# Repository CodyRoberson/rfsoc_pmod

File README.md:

## ZCU111 RFSOC PMOD BREAKOUT BOARD
KiCad 6 design.

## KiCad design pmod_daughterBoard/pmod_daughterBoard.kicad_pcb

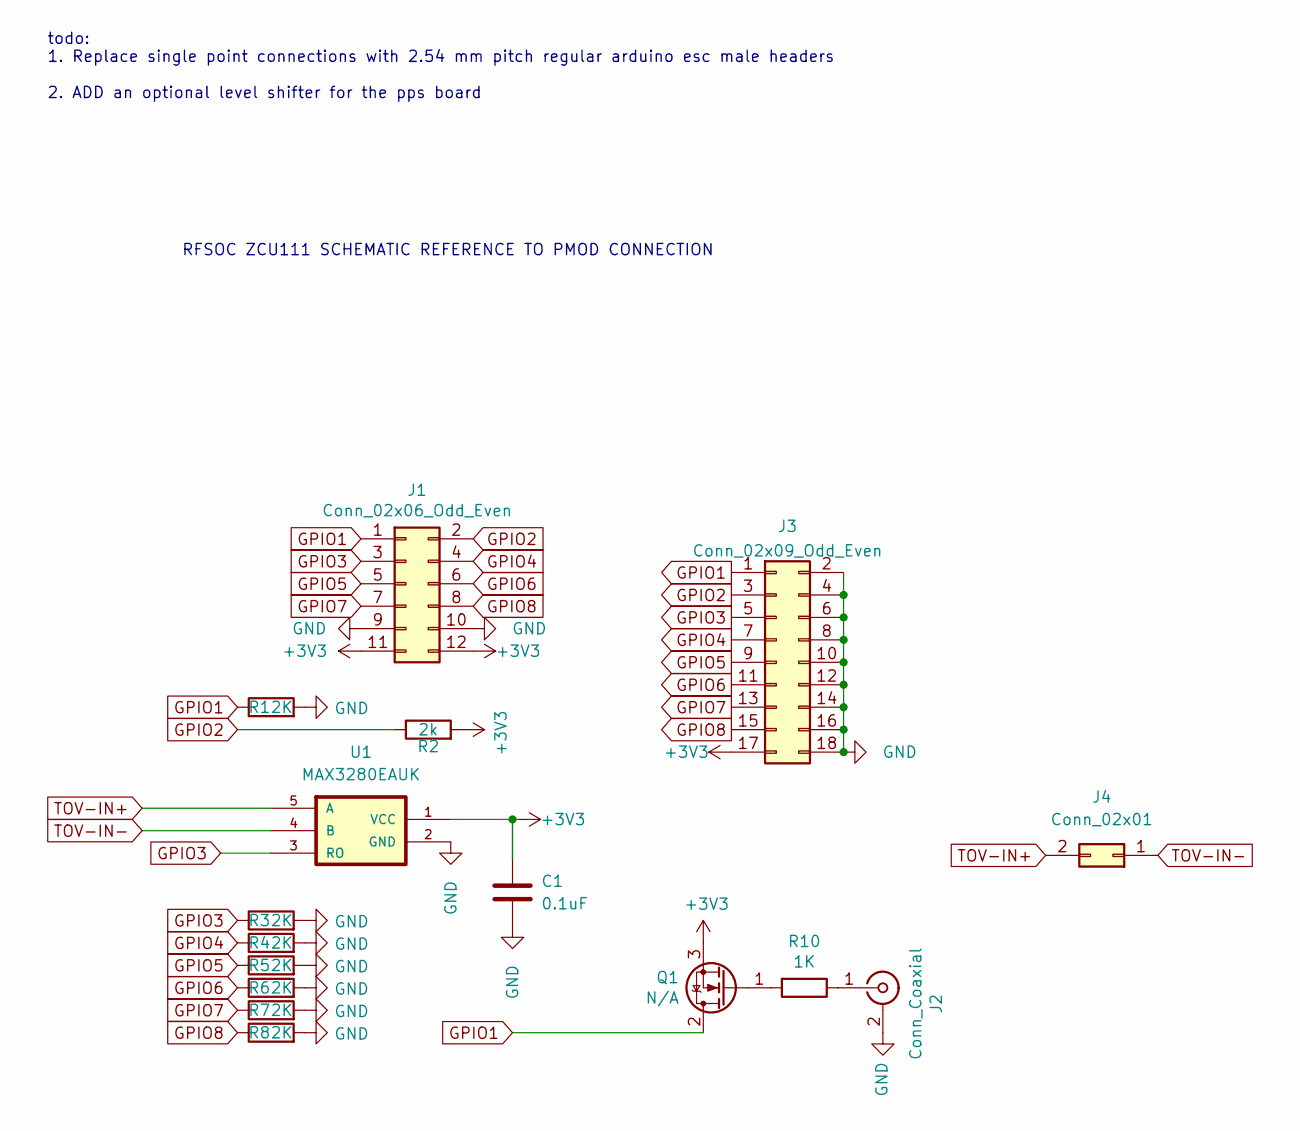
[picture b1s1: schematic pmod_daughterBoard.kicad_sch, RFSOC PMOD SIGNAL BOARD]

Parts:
C1: 0.1uF; C_0402_1005Metric
J1: Conn_02x06_Odd_Even; PinHeader_2x06_P2.54mm_Horizontal
J2: Conn_Coaxial; LINX_CONSMA001-SMD-G-T
J3: Conn_02x09_Odd_Even; PinHeader_2x09_P2.54mm_Vertical
J4: Conn_02x01; PinHeader_2x01_P2.54mm_Vertical
Q1: N/A; SOT-23; Part Number 78-SI2318DS-T1-BE3
R1, R3, R4, R5, R6, R7, R8: 2K; R_0402_1005Metric; Part Number 603-AC0402JR-072KL
R2: 2k; R_0402_1005Metric
R10: 1K; R_0402_1005Metric
U1: MAX3280EAUK; SOT95P280X145-5N; Part Number MAX3280EAUK+T

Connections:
+3V3: C1.2, J1.11, J1.12, J3.17, Q1.3 (S), R2.2, U1.1 (VCC)
GND: C1.1, J1.9, J1.10, J2.2 (Ext), J3.2, J3.4, J3.6, J3.8, J3.10, J3.12, J3.14, J3.16, J3.18, R1.2, R3.2, R4.2, R5.2, R6.2, R7.2, R8.2, U1.2 (GND)
GPIO1: J1.1, J3.1, Q1.2 (D), R1.1
GPIO2: J1.2, J3.3, R2.1
GPIO3: J1.3, J3.5, R3.1, U1.3 (RO)
GPIO4: J1.4, J3.7, R4.1
GPIO5: J1.5, J3.9, R5.1
GPIO6: J1.6, J3.11, R6.1
GPIO7: J1.7, J3.13, R7.1
GPIO8: J1.8, J3.15, R8.1
unnamed: J2.1 (In), R10.1
unnamed: Q1.1 (G), R10.2
TOV-IN+: J4.2, U1.5 (A)
TOV-IN-: J4.1, U1.4 (B)

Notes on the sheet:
RFSOC ZCU111 SCHEMATIC REFERENCE TO PMOD CONNECTION
todo: 1. Replace single point connections with 2.54 mm pitch regular arduino esc male headers 2. ADD an optional level shifter for the pps board

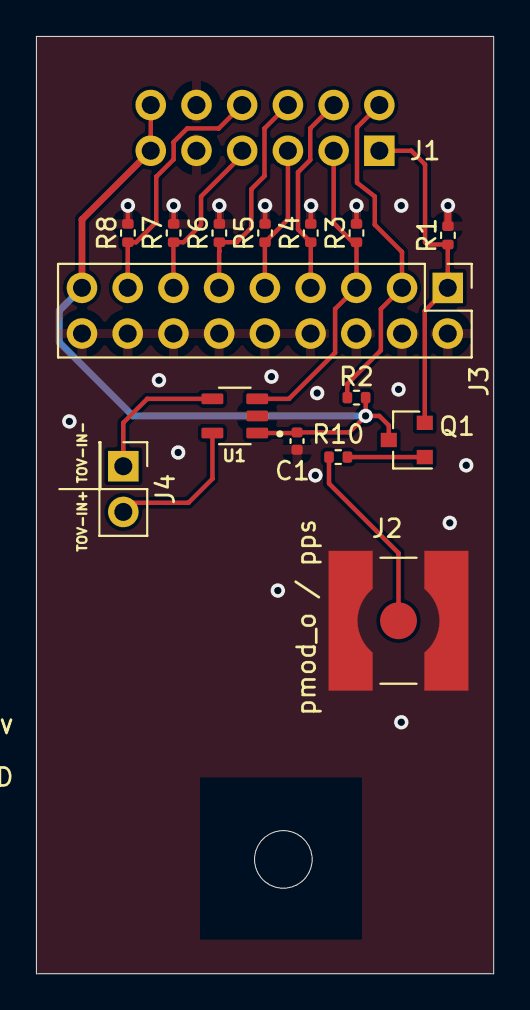
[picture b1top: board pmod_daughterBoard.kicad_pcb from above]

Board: 2 copper layers, 25.4 x 52.1 mm, 16 parts (1 on the bottom side), 14 nets.

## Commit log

2022-02-28 init
2022-03-04 update board
2022-07-01 began implementation of various gpio inputs. Removed redundant GND resistor
2022-07-05 implemented differential pair receiver on pmod board
